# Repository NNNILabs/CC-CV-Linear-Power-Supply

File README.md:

# CC CV Linear Power Supply
## Clean and elegant CC CV linear supply, no weird biasing or floating stuff.

I designed this power supply to replace the hacked-together ATX/buck-boost/LT3081 I was using. 
The goal from the beginning was simplicity and to use parts that are easily available, such as those from the JLCPCB parts library.

It is "modular" in the sense that only the op-amps and the associated feedback circuitry were meant to be JLC assmebled, with the MOSFETs, input/output electrolytics, current shunts and protection diodes being added by the user.

Since the parts and topology used are rather straightforward, this thing can even be built on a perfboard (I tried, it worked).

Capabilities:
- Output voltage - 0V to 30V, with "true" 0V (load and MOSFET leakage dependent)
- Output current - 0A to (500mV/Rshunt)A, maximum (limited by parts on the board) 6A per rail, with both MOSFETs populated
- Input voltage - up to 50V

**Important - to make full use of the output voltage and current ranges, the MOSFETs *must* be heatsinked.**

Circuit details:
- 5V for op-amps and reference: 2x 5V regulators to reduce heat dissipation, with an input pre-regulator based on the TL431 so that the 5V regulator's maximum input voltage is not exceeded (in this case 24V) as well as to spread the power dissipation between more parts to reduce temperature rise. Jumper J1 can be shorted if the input voltage is below the maximum rated input voltage for the 5V regulator being used, this reduces input quiescent current.
- Buffered references: The output voltage and current are set using two potentiometers. Since the potentiometers are connected to 5V, the reference voltages for CC and CV are 0V to 5V. The potentiometer outputs are buffered using a dual RRIO op-amp to prevent loading (and therefore errors). This means that the output voltage and current are *independent* of the potentiometer value, but make sure that the current consumed by both potentiometers does not exceed 1mA (or a minimum potentiometer resistance of 5K).
- +CV - straightforward op-amp circuit that compares the CV reference to an output divider
- +CC - a differential amplifier that forms a Howland current source, threshold set by CV reference
- -CV and -CC are not very straightforward - CV forms a "null detector" that tries to maintain 0V at the summing junction of the CV reference and output voltage through appropriately scaled resistors, while the CC differential amplifier sets the summing junction voltage, increasing it if the current limit is reached and therefore reducing output voltage
- MOSFET gate driver - a slightly modified "AB" amplifier to increase the op-amp output current enough to drive the MOSFET gate to higher voltages.

Quirks:
- Minimum -CC threshold is 120mA, for some reason.

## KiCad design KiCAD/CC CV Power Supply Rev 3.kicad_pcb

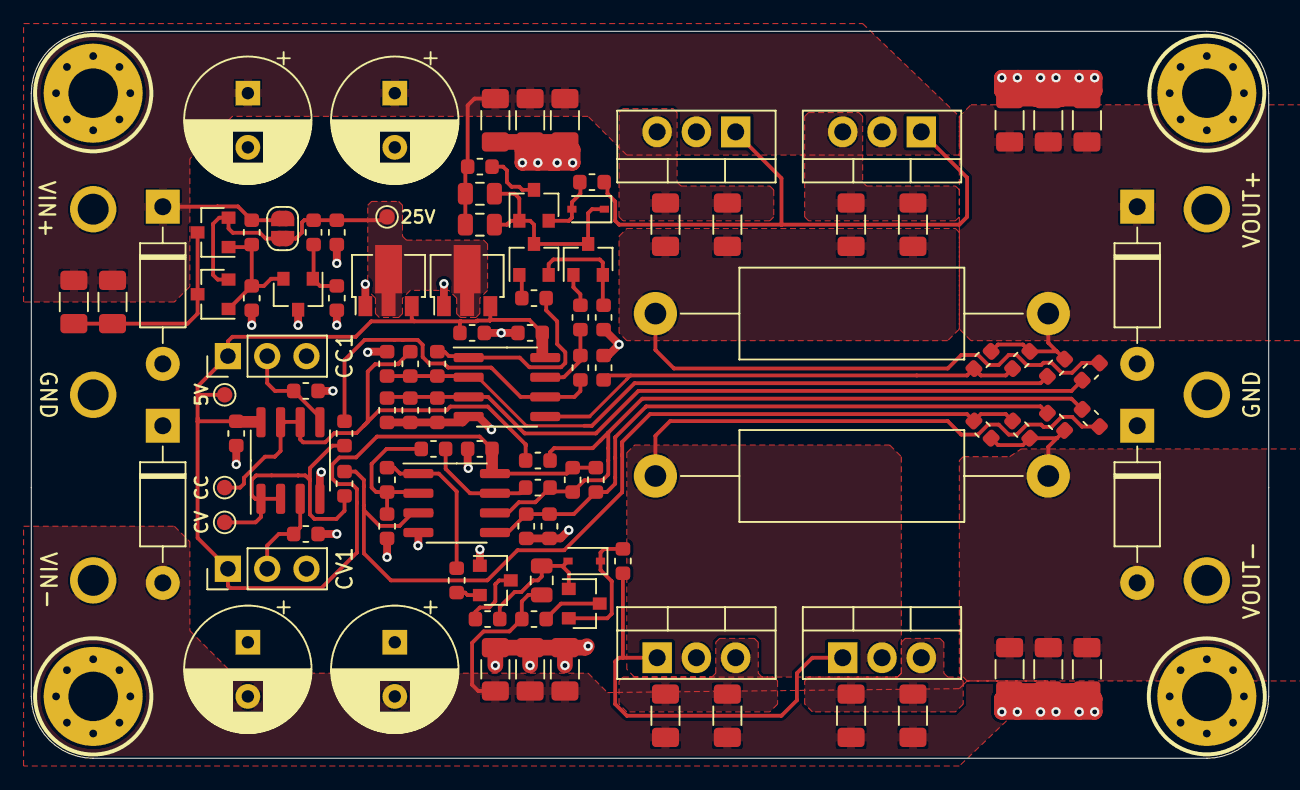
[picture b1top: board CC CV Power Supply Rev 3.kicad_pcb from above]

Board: 2 copper layers, 80.0 x 47.0 mm, 118 parts (0 on the bottom side), 45 nets.

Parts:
C1, C2, C3, C11: 22uF; C_0603_1608Metric
C4, C5, C28, C29: 100uF; CP_Radial_D8.0mm_P3.50mm
C6, C32: 1uF; C_0603_1608Metric
C7, C8, C9, C10, C12, C13, C20, C21, C22, C23, C24, C25: 10uF; C_1206_3216Metric
C14, C15, C16, C17, C18, C19, C30, C31: 1nF; C_0603_1608Metric
C26, C27: 100nF; C_0603_1608Metric
CC1: 10K; PinHeader_1x03_P2.54mm_Vertical
CV1: 10K; PinHeader_1x03_P2.54mm_Vertical
D1, D2, D3, D4: 1N4007; D_DO-41_SOD81_P10.16mm_Horizontal
D5, D6: 1N4148; D_SOD-323
H1: VIN+; MountingHole_2.2mm_M2_DIN965_Pad
H2, H10: GND; MountingHole_2.2mm_M2_DIN965_Pad
H4: VIN-; MountingHole_2.2mm_M2_DIN965_Pad
H5, H6, H7, H8: MountingHole; MountingHole_3.2mm_M3_Pad_Via
H9: VOUT+; MountingHole_2.2mm_M2_DIN965_Pad
H11: VOUT-; MountingHole_2.2mm_M2_DIN965_Pad
JP1: VIN; SolderJumper-2_P1.3mm_Open_RoundedPad1.0x1.5mm
Q1, Q3, Q8, Q10, Q11: 5551; SOT-23
Q2, Q9: 5401; SOT-23
Q4, Q5, Q6, Q7: NMOS; TO-220-3_Vertical
R1, R11, R19, R49, R50: 10K; R_0603_1608Metric
R2: 22K; R_0603_1608Metric
R3, R10, R20, R23, R24, R30, R31: 2K; R_0603_1608Metric
R4: 10K; R_0805_2012Metric
R5, R29: 20K; R_0805_2012Metric
R6, R9, R14, R36, R51: 1K; R_0603_1608Metric
R7, R8, R12, R13, R37, R38, R39, R40: 0R1; R_1206_3216Metric
R15, R16: 100K; R_0603_1608Metric
R17, R18: 120K; R_0603_1608Metric
R21, R28: 750R; R_1206_3216Metric
R22, R34, R47, R48: 10R; R_0603_1608Metric
R25, R32, R35: 12K; R_0603_1608Metric
R26, R27: 0R1; R_Axial_DIN0614_L14.3mm_D5.7mm_P25.40mm_Horizontal
R52, R53: 220R; R_0603_1608Metric
TP1: 5V; TestPoint_Pad_D1.0mm
TP2: 30V; TestPoint_Pad_D1.0mm
TP3: CVREF; TestPoint_Pad_D1.0mm
TP4: CCREF; TestPoint_Pad_D1.0mm
U1, U2, U4: MCP6002; SOIC-8_3.9x4.9mm_P1.27mm
U3: TL431; SOT-23
U5, U6: HT7550; SOT-89-3

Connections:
+5V: C1.2, C2.1, C3.2, C11.2, CC1.1, CV1.1, R24.1, R31.1, TP1.1, U1.8, U2.8, U4.8, U5.3, U6.3
CC_REF: R16.2, R18.2, TP4.1, U4.6, U4.7
CV_REF: R10.1, R36.1, TP3.1, U4.1, U4.2
GND: C1.1, C2.2, C3.1, C4.2, C5.1, C6.2, C7.1, C8.1, C9.1, C10.1, C11.1, C12.1, C13.1, C15.2, C18.2, C20.1, C21.1, C22.1, C23.1, C24.1, C25.1, C26.1, C27.2, C28.2, C29.1, C32.2, CC1.3, CV1.3, D1.2, D2.1, D3.2, D4.1, H2.1, H10.1, Q9.1, R3.2, R11.2, R15.2, R17.2, R20.2, R23.2, R30.2, R48.2, U1.4, U2.4, U3.3, U4.4, U5.1, U6.1
unnamed: C6.1, JP1.2, Q1.2, Q11.2, R2.1, TP2.1, U5.2, U6.2
unnamed: C5.2, C8.2, C10.2, C13.2, C29.2, D2.2, H4.1, R4.2, R7.2, R8.2, R34.2, R39.2, R40.2
unnamed: C4.1, C7.2, C9.2, C12.2, C28.1, D1.1, H1.1, JP1.1, Q6.2, Q7.2, R1.1, R5.1, R21.2, R28.2, R29.1, R47.1
unnamed: C14.1, R6.1, U2.1
unnamed: C14.2, R11.1, R51.2, U2.2
unnamed: C15.1, R15.1, R23.1, R49.2, U1.3
unnamed: C16.1, R14.1, U1.1
unnamed: C16.2, R16.1, R30.1, R50.2, U1.2
unnamed: C17.1, R9.1, U1.7
unnamed: C17.2, R36.2, U1.6
unnamed: C18.1, R17.1, R31.2, R32.1, U2.5
unnamed: C19.1, R51.1, U2.7
unnamed: C19.2, R18.1, R24.2, R25.1, U2.6
unnamed: C20.2, C22.2, C24.2, C30.1, D3.1, H9.1, R19.2, R26.2, R50.1
unnamed: C21.2, C23.2, C25.2, C31.2, D4.2, H11.1, R27.2, R32.2, R35.2
unnamed: C26.2, CV1.2, U4.3
unnamed: C27.1, CC1.2, U4.5
unnamed: C30.2, R19.1, R20.1, U1.5
unnamed: C31.1, R10.2, R35.1, U2.3
unnamed: C32.1, Q1.1, Q11.1, R1.2, U3.1
unnamed: D5.1, Q2.2, R53.2
unnamed: D5.2, Q2.1, R4.1, R22.2
unnamed: D6.1, Q3.3, Q8.3, Q10.1, R5.2, R29.2
unnamed: D6.2, Q10.2, R52.2
unnamed: Q1.3, Q11.3, R21.1, R28.1
unnamed: Q2.3, R34.1
unnamed: Q3.1, R9.2
unnamed: Q3.2, Q8.2, R48.1
unnamed: Q4.1, Q5.1, R53.1
unnamed: Q4.2, Q5.2, R25.2, R27.1
unnamed: Q4.3, R7.1, R39.1
unnamed: Q5.3, R8.1, R40.1
unnamed: Q6.1, Q7.1, R52.1
unnamed: Q6.3, R12.2, R37.2
unnamed: Q7.3, R13.2, R38.2
unnamed: Q8.1, R14.2
unnamed: Q9.2, R6.2
unnamed: Q9.3, R22.1
unnamed: Q10.3, R47.2
unnamed: R2.2, R3.1, U3.2
unnamed: R12.1, R13.1, R26.1, R37.1, R38.1, R49.1

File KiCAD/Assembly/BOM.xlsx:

Comment | Designator | Footprint | LCSC Part #
22uF Unpolarized capacitor | C1,C2,C3,C11 | C_0603_1608Metric | C59461
100uF Polarized capacitor | C4,C5,C28,C29 | CP_Radial_D8.0mm_P3.50mm
1uF Unpolarized capacitor | C6,C32 | C_0603_1608Metric | C15849
10uF Unpolarized capacitor | C7,C8,C9,C10,C12,C13,C20,C21,C22,C23,C24,C25 | C_1206_3216Metric | C13585
1nF Unpolarized capacitor | C14,C15,C16,C17,C18,C19,C30,C31 | C_0603_1608Metric | C1588
100nF Unpolarized capacitor | C26,C27 | C_0603_1608Metric | C14663
10K Potentiometer | CC1,CV1 | PinHeader_1x03_P2.54mm_Vertical
1N4007 Diode | D1,D2,D3,D4 | D_DO-41_SOD81_P10.16mm_Horizontal
1N4148 Diode | D5,D6 | D_SOD-323 | C2128
VIN+ Mounting Hole with connection | H1 | MountingHole_2.2mm_M2_DIN965_Pad
GND Mounting Hole with connection | H2,H10 | MountingHole_2.2mm_M2_DIN965_Pad
VIN- Mounting Hole with connection | H4 | MountingHole_2.2mm_M2_DIN965_Pad
MountingHole Mounting Hole without connection | H5,H6,H7,H8 | MountingHole_3.2mm_M3_Pad_Via
VOUT+ Mounting Hole with connection | H9 | MountingHole_2.2mm_M2_DIN965_Pad
VOUT- Mounting Hole with connection | H11 | MountingHole_2.2mm_M2_DIN965_Pad
VIN Solder Jumper, 2-pole, open | JP1 | SolderJumper-2_P1.3mm_Open_RoundedPad1.0x1.5mm
5551 NPN transistor, base/emitter/collector | Q1,Q3,Q8,Q10,Q11 | SOT-23 | C2145
5401 PNP transistor, base/emitter/collector | Q2,Q9 | SOT-23 | C8326
NMOS N-MOSFET transistor, gate/drain/source | Q4,Q5,Q6,Q7 | TO-220-3_Vertical
10K Resistor | R1,R11,R19,R49,R50 | R_0603_1608Metric | C25804
18K Resistor | R2 | R_0603_1608Metric | C25810
2K Resistor | R3,R10,R20,R23,R24,R30,R31 | R_0603_1608Metric | C22975
10K Resistor | R4 | R_0805_2012Metric | C17414
20K Resistor | R5,R29 | R_0805_2012Metric | C4328
1K Resistor | R6,R9,R14,R36,R51 | R_0603_1608Metric | C21190
0R1 Resistor | R7,R8,R12,R13,R37,R38,R39,R40 | R_1206_3216Metric | C25334
100K Resistor | R15,R16 | R_0603_1608Metric | C25803
120K Resistor | R17,R18 | R_0603_1608Metric | C25808
750R Resistor | R21,R28 | R_1206_3216Metric | C17985
10R Resistor | R22,R34,R47,R48 | R_0603_1608Metric | C22859
12K Resistor | R25,R32,R35 | R_0603_1608Metric | C22790
0R1 Resistor | R26,R27 | R_Axial_DIN0614_L14.3mm_D5.7mm_P25.40mm_Horizontal
220R Resistor | R52,R53 | R_0603_1608Metric | C22962
5V test point | TP1 | TestPoint_Pad_D1.0mm
25V test point | TP2 | TestPoint_Pad_D1.0mm
CVREF test point | TP3 | TestPoint_Pad_D1.0mm
CCREF test point | TP4 | TestPoint_Pad_D1.0mm
MCP6002 1MHz, Low-Power Op Amp, SOIC-8 | U1,U2,U4 | SOIC-8_3.9x4.9mm_P1.27mm | C7377
TL431 Shunt Regulator, SOT-23 | U3 | SOT-23 | C3113
HT7550 100mA Low Dropout Voltage Regulator, Fixed Output, SOT89 | U5,U6 | SOT-89-3 | C16106
